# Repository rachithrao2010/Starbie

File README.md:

Hey! This project was built as a part of Hack Club Half Life. It was originally intended to be a tamagotchi toy, but i instead turned it into a short, pokemon style game. 

You start out with the character blobb (who is essentially a blob) and once you win a battle, the game lets you evolve it into a Blocky  (who is made of striaght lines) OR a spiky (who is spiky).
Winning further battles lets you evolve your character, and including the initial stage, there are 3 evolutions of each character.

Battles have also been changed from a your character vs. other character battle to a your character vs. AI Tic-tac-toe game.

You control the Tic-Tac-toe game by tilting the entire pcb. once you're in the right position, click the top switch to lock it in. The AI then does its turn, and the battle continues like this.

Visit https://wokwi.com/projects/477641998977817601 to test it out virtually, meaning you don't even need the pcb! To do this, click the green play button in the  top left of the hardware panel. You can then just left click the accelerometer (which is the blue chip near the very top) and change the rotation bars to "Tilt" the accelerometer. SW1 is the top switch, and SW2 is the bottom switch.

The online simulation should look like this:

Here's a 3D render of the pcb!

And here's a BOM

| Item | Qty | Supplier | Cost/item | Total Cost | Link |
|---|---:|---|---:|---:|---|
| Header Pins | 1 | TLZWLA Official Store | $1.39 | $1.39 | [Link](https://www.aliexpress.us/item/3256805072379643.html?spm=a2g0o.cart.0.0.106c38daIS6h4V&mp=1&pdp_npi=6%40dis%21USD%21USD+1.39%21USD+1.39%21%21USD+1.39%21%21%21%402101ea8f17928801450344904e09f1%2112000032390031595%21ct%21US%218282744365%21%211%210%21&_gl=1*1yuvcyf*_gcl_au*Mjg4MjIyMTY4LjE3OTE3NjI1MDg.*_ga*MTAzODc3Mzk3MS4xNzkxNzc1MzQ2*_ga_VED1YSGNC7*czE3OTI4Nzk4NjYkbzQkZzEkdDE3OTI4ODAxNDkkajMkbDAkaDA.&gatewayAdapt=glo2usa) |
| DHT11 | 1 | Lucky Electonics Components Store | $1.66 | $1.66 | [Link](https://www.aliexpress.us/item/3256808602611303.html?spm=a2g0o.cart.0.0.106c38daIS6h4V&mp=1&pdp_npi=6%40dis%21USD%21USD+1.66%21USD+1.66%21%21USD+1.66%21%21%21%402101ea8f17928801450344904e09f1%2112000046667765928%21ct%21US%218282744365%21%211%210%21&_gl=1*66ti7f*_gcl_au*Mjg4MjIyMTY4LjE3OTE3NjI1MDg.*_ga*MTAzODc3Mzk3MS4xNzkxNzc1MzQ2*_ga_VED1YSGNC7*czE3OTI4Nzk4NjYkbzQkZzEkdDE3OTI4ODAyMTIkajM1JGwwJGgw&gatewayAdapt=glo2usa) |
| MPU6050 | 1 | Nextronics Store | $1.09 | $1.09 | [Link](https://www.aliexpress.us/item/3256812536361672.html?spm=a2g0o.cart.0.0.106c38daIS6h4V&mp=1&pdp_npi=6%40dis%21USD%21USD+3.88%21USD+1.09%21%21USD+1.09%21%21%21%402101ea8f17928801450344904e09f1%2112000059167286842%21ct%21US%218282744365%21%211%210%21&_gl=1*1zokem*_gcl_au*Mjg4MjIyMTY4LjE3OTE3NjI1MDg.*_ga*MTAzODc3Mzk3MS4xNzkxNzc1MzQ2*_ga_VED1YSGNC7*czE3OTI4Nzk4NjYkbzQkZzEkdDE3OTI4ODAyMTYkajMxJGwwJGgw&gatewayAdapt=glo2usa) |
| Keycaps | 1 | SZ Electronic Store | $3.76 | $3.76 | [Link](https://www.aliexpress.us/item/3256808640925468.html?spm=a2g0o.cart.0.0.106c38daIS6h4V&mp=1&pdp_npi=6%40dis%21USD%21USD+3.76%21USD+3.76%21%21USD+3.76%21%21%21%402101ea8f17928801450344904e09f1%2112000046843776637%21ct%21US%218282744365%21%211%210%21&_gl=1*11iiwlw*_gcl_au*Mjg4MjIyMTY4LjE3OTE3NjI1MDg.*_ga*MTAzODc3Mzk3MS4xNzkxNzc1MzQ2*_ga_VED1YSGNC7*czE3OTI4Nzk4NjYkbzQkZzEkdDE3OTI4ODAyNjkkajYwJGwwJGgw&gatewayAdapt=glo2usa) |
| OLED | 1 | AOKIN | $0.33 | $0.33 | [Link](https://github.com/user-attachments/assets/14cdffc6-8f83-4813-89f4-dde2b5d74e93) |
| ESP32-C3 | 1 | TENSTAR | $0.33 | $0.33 | [Link](https://private-user-images.githubusercontent.com/164773739/672871541-c80409e2-514a-4e3d-b252-5cad1b38e64b.png?jwt=eyJ0eXAiOiJKV1QiLCJhbGciOiJIUzI1NiJ9.eyJpc3MiOiJnaXRodWIuY29tIiwiYXVkIjoicmF3LmdpdGh1YnVzZXJjb250ZW50LmNvbSIsImtleSI6ImtleTUiLCJleHAiOjE3OTMxMDYzMDgsIm5iZiI6MTc5MzEwNjAwOCwicGF0aCI6Ii8xNjQ3NzM3MzkvNjcyODcxNTQxLWM4MDQwOWUyLTUxNGEtNGUzZC1iMjUyLTVjYWQxYjM4ZTY0Yi5wbmc_WC1BbXotQWxnb3JpdGhtPUFXUzQtSE1BQy1TSEEyNTYmWC1BbXotQ3JlZGVudGlhbD1BS0lBVkNPRFlMU0E1M1BRSzRaQSUyRjIwMjYxMDI3JTJGdXMtZWFzdC0xJTJGczMlMkZhd3M0X3JlcXVlc3QmWC1BbXotRGF0ZT0yMDI2MTAyN1QxMzAwMDhaJlgtQW16LUV4cGlyZXM9MzAwJlgtQW16LVNpZ25hdHVyZT1hZWNlN2M2ZGM5NzNiYTU2N2U3NzM5NWExNDhhZjY5MmEzZWU5Y2ZhMzc3MDg5MzhmYWU0ZmRkOTY4ZTdhMGVmJlgtQW16LVNpZ25hdHVyZT1ob3N0JnJlc3BvbnNlLWNvbnRlbnQtdHlwZT1pbWFnZSUyRnBuZyJ9.U13o_11bhSQt8wXuSKkY2WW7yLKLWrsNO1zDX7EUgUU) |
| Switches | 1 | Outemu | $0.33 | $0.33 | [Link](https://private-user-images.githubusercontent.com/164773739/672871854-12fde47a-c655-4e76-a2a4-1efece8db0de.png?jwt=eyJ0eXAiOiJKV1QiLCJhbGciOiJIUzI1NiJ9.eyJpc3MiOiJnaXRodWIuY29tIiwiYXVkIjoicmF3LmdpdGh1YnVzZXJjb250ZW50LmNvbSIsImtleSI6ImtleTUiLCJleHAiOjE3OTMxMDYzMDgsIm5iZiI6MTc5MzEwNjAwOCwicGF0aCI6Ii8xNjQ3NzM3MzkvNjcyODcxODU0LTEyZmRlNDdhLWM2NTUtNGU3Ni1hMmE0LTFlZmVjZThkYjBkZS5wbmc_WC1BbXotQWxnb3JpdGhtPUFXUzQtSE1BQy1TSEEyNTYmWC1BbXotQ3JlZGVudGlhbD1BS0lBVkNPRFlMU0E1M1BRSzRaQSUyRjIwMjYxMDI3JTJGdXMtZWFzdC0xJTJGczMlMkZhd3M0X3JlcXVlc3QmWC1BbXotRGF0ZT0yMDI2MTAyN1QxMzAwMDhaJlgtQW16LUV4cGlyZXM9MzAwJlgtQW16LVNpZ25hdHVyPWNmMTA1MmVjNzhlYzUwMTM4MmM1YjBhNzY2OGUxMjAwYWQwYTIxNDkwMzAyNjk3MjY2MGEzMGY0NjlmYTU1YWJhJlgtQW16LVNpZ25hdHVyZT1ob3N0JnJlc3BvbnNlLWNvbnRlbnQtdHlwZT1pbWFnZSUyRnBuZyJ9.iy8f5l0IxWf8MuJRQKw5BXrbHxTymNsu2pK8VWgY2Wk) |
| Estimated total shipping | 1 |  |  | $0.00 |  |

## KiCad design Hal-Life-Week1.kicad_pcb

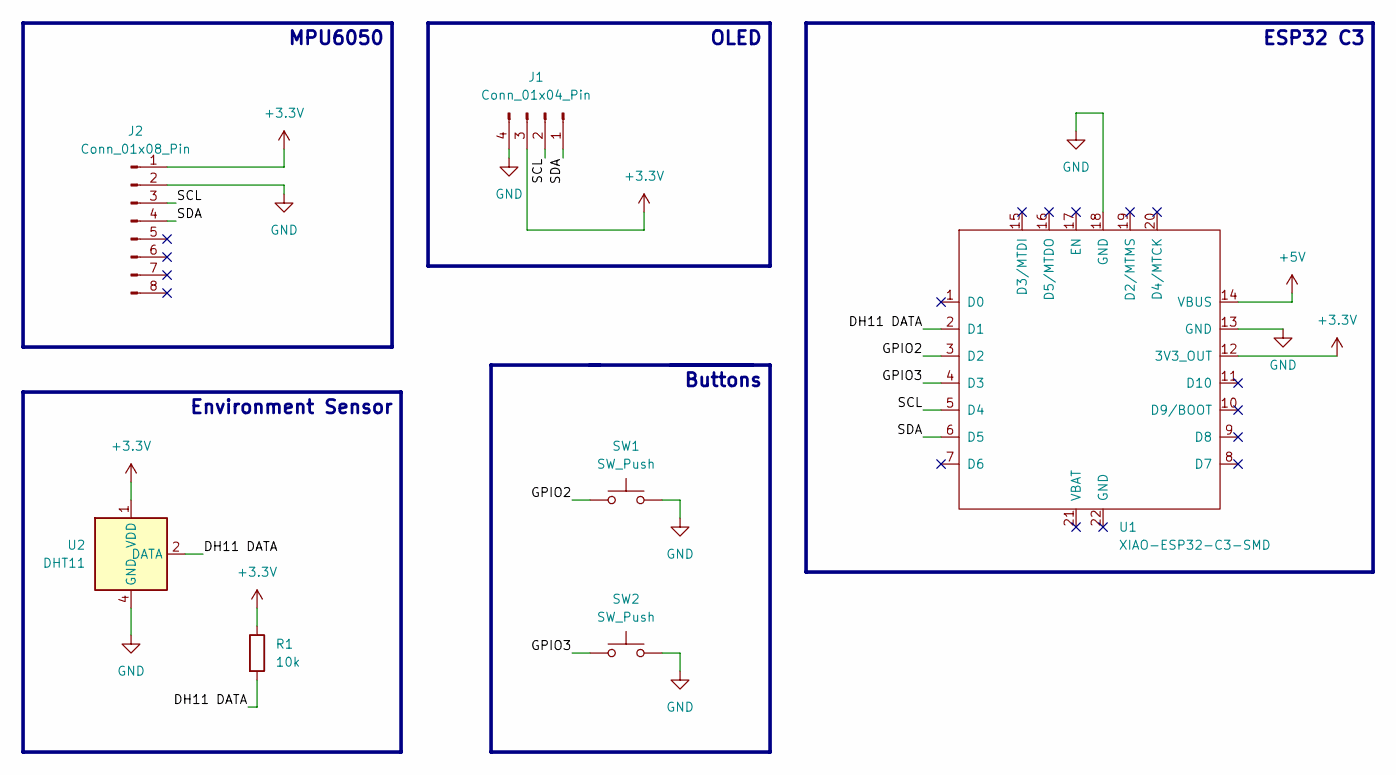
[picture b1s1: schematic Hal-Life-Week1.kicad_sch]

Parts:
J1: Conn_01x04_Pin; Display_128x64_096_I2C
J2: Conn_01x08_Pin; PinHeader_1x08_P2.54mm_Vertical
R1: 10k; R_Axial_DIN0204_L3.6mm_D1.6mm_P7.62mm_Horizontal
SW1, SW2: SW_Push; SW_Cherry_MX_1.00u_PCB
U1: XIAO-ESP32-C3-SMD
U2: DHT11; Aosong_DHT11_5.5x12.0_P2.54mm

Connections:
+3.3V: J1.3, J2.1, R1.1, U1.12 (3V3_OUT), U2.1 (VDD)
+5V: U1.14 (VBUS)
/DH11 DATA: R1.2, U1.2 (D1), U2.2 (DATA)
/GPIO2: SW1.1, U1.3 (D2)
/GPIO3: SW2.1, U1.4 (D3)
/SCL: J1.2, J2.3, U1.5 (D4)
/SDA: J1.1, J2.4, U1.6 (D5)
GND: J1.4, J2.2, SW1.2, SW2.2, U1.13 (GND), U1.18 (GND), U2.4 (GND)

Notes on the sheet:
OLED
MPU6050
Environment Sensor
Buttons
ESP32 C3

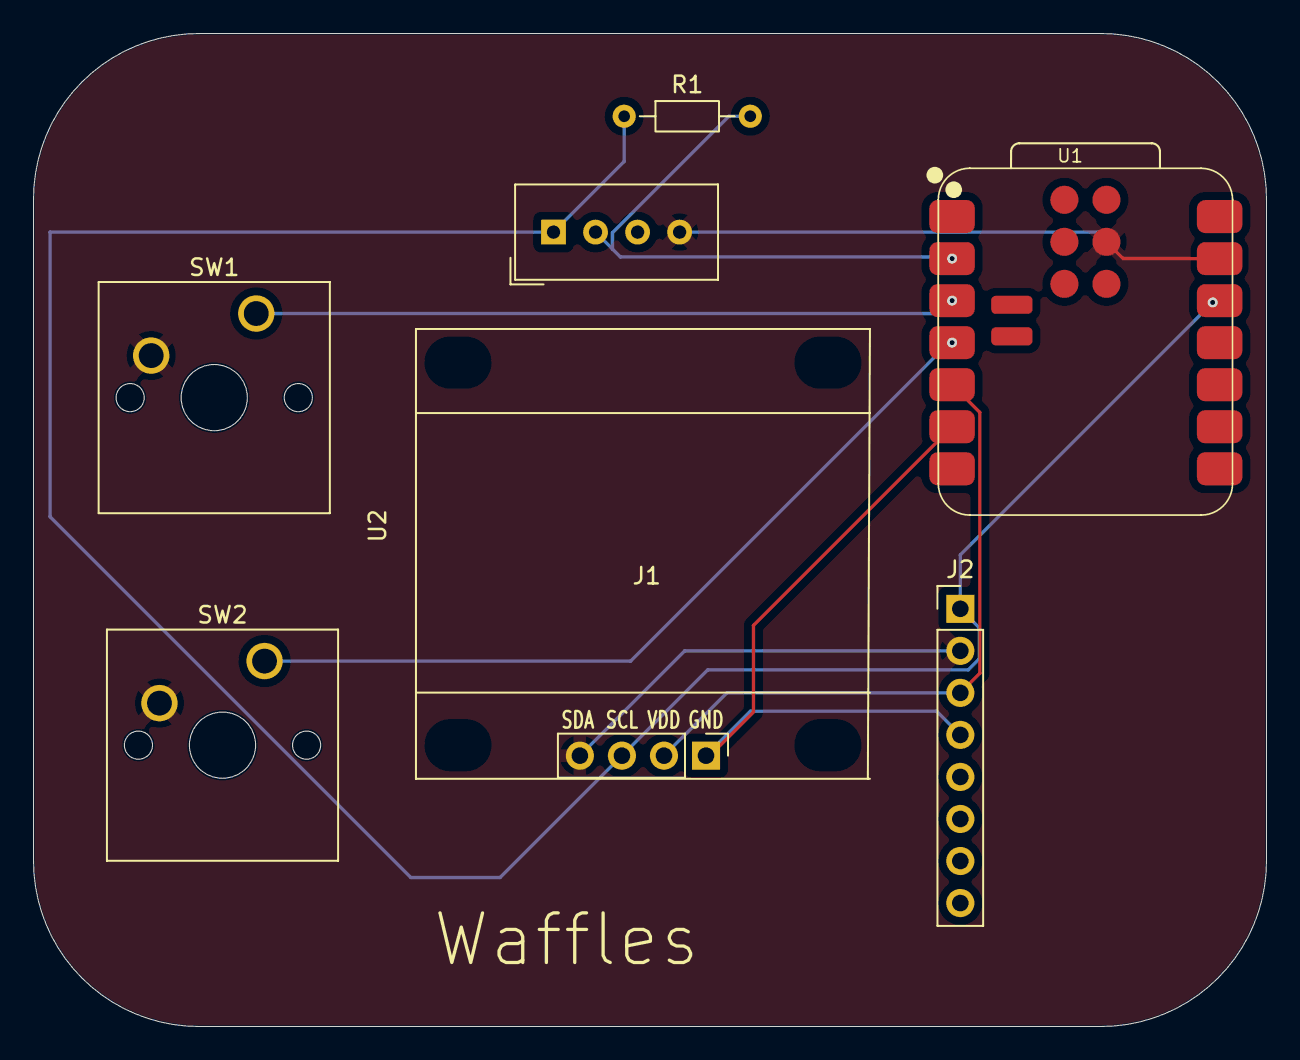
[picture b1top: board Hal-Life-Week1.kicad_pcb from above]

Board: 2 copper layers, 74.5 x 60.0 mm, 7 parts (0 on the bottom side), 7 nets.
